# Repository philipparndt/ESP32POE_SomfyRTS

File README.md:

# ESP32 PoE Somfy RTS Bridge

# Not yet verified

This header is currently work in progress and not yet tested/verified.

## Partlist

- [ESP32 PoE](https://www.olimex.com/Products/IoT/ESP32/ESP32-POE/open-source-hardware)
- UEXT connector HIF3FB-10DA-2.54DSA(69)
- Ebyte [E07-433M20S](https://www.cdebyte.com/products/E07-433M20S)
- 433MHz Antenna

## Shield variants

### ESP32SomfyPOE

- C1101 radio module is mounted on the top side of the board
- One mounting hole for the header
- Length smaller than the ESP32 PoE board,
  fits in a [Raspberry Pi case](https://www.amazon.de/dp/B07CN5XYBN) or a junction box

### ESP32SomfyPOE_bottom

- C1101 radio module is mounted on the bottom side of the board
- Smaller height than the ESP32SomfyPOE variant
- One mounting hole for the header
- Length smaller than the ESP32 PoE board,
  fits in a [Raspberry Pi case](https://www.amazon.de/dp/B07CN5XYBN) or a junction box

### ESP32SomfyPOE_rotated

- Smallest variant, but no mounting hole for the header
- Ideal for a 3D printed case

## Software

https://github.com/rstrouse/ESPSomfy-RTS

## Configuration

### Radio

| Parameter | Value   |
| --------- | ------- |
| SCLK      | GPIO_14 |
| CSN       | GPIO_13 |
| MOSI      | GPIO_15 |
| MISO      | GPIO_16 |
| TX        | GPIO_04 |
| RX        | GPIO_36 |

### Network

| Parameter  | Value       |
| ---------- | ----------- |
| PHY Chip   | LAN8720     |
| Address    | PHY 0       |
| Clock Mode | GPIO_17 OUT |
| Power Pin  | GPIO_12     |
| MDC Pin    | GPIO_23     |
| MDIO Pin   | GPIO_18     |

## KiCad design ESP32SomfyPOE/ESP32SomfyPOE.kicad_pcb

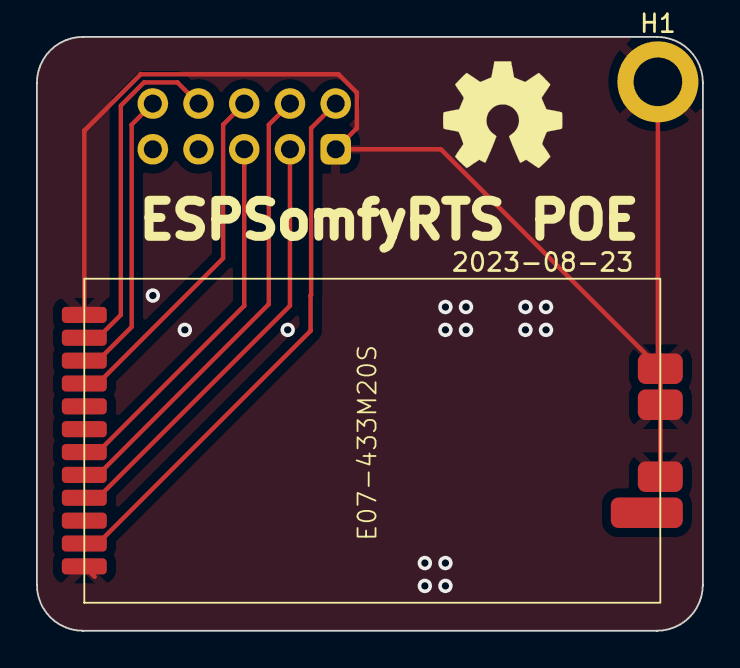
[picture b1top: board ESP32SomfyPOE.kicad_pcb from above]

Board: 2 copper layers, 37.0 x 33.0 mm, 4 parts (1 on the bottom side), 8 nets.

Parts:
E07-433M20S: E07-433M20S
H1: MountingHole_Pad; MountingHole_2.7mm_M2.5_ISO14580_Pad
N1: Housing; OSHW-Symbol_6.7x6mm_SilkScreen
UEXT: UEXT_Host; IDC-Stecker_2x05_P2.54mm_Vertical

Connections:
+3V3: E07-433M20S.11 (VCC), UEXT.1 (3V3)
GND: E07-433M20S.1 (GND), E07-433M20S.12 (GND), E07-433M20S.14 (GND), E07-433M20S.15 (GND), E07-433M20S.16 (GND), H1.1, UEXT.2 (GND)
GPI36: E07-433M20S.9 (RX_EN), UEXT.4 (RXD)
GPIO4: E07-433M20S.8 (TX_EN), UEXT.3 (TXD)
GPIO13: E07-433M20S.7 (CSN), UEXT.6 (SDA)
GPIO14: E07-433M20S.3 (SCK), UEXT.9 (SCK)
GPIO15: E07-433M20S.2 (MOSI), UEXT.7 (MISO)
GPIO16: E07-433M20S.4 (MISO), UEXT.5 (SCL)

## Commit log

2023-08-24 Initial version
2023-08-24 add test action
2023-08-24 Add renovate.json
2023-08-24 Initial version
    add test action
    kibot
    -
